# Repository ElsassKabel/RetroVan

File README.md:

# RetroVan
🚐 *Retro style [Minivan](https://trashman.wiki/keyboards/minivan) keyboard*

| Front side | Back side |
| ----- | ----- |
|  |  |

<!-- ## ✨ Pros:

- 🌈 Easy to customize with QMK and Vial
- 💅 Compact and beautiful
- 🦄 Open source -->

## 📖 Documentation

*🚧 WIP*

| Name | Supported layout |
| ----- | ----- |
| A | 1, 2 |
| B | 3, 4, 5 |
| C | 6, 7 |

<!-- ## 👀 Showcase -->

## 👤 Author

**LucasAlt**
* Website: https://www.lucasalt.fr
* Twitter: [@LucasCtrlAlt](https://twitter.com/LucasCtrlAlt)
* GitHub: [@LucasCtrl](https://github.com/LucasCtrl)

<!-- ## 🙏 Thanks
* [**@username**](https://github.com/username) - What I do
* [And many more!](https://github.com/ElsassKabel/RetroVan/graphs/contributors) -->

## 🤝 Contributing

<!-- Before contributing to this project, make sure you have read the [contribution guidelines](https://github.com/ElsassKabel/RetroVan/blob/main/CONTRIBUTING.md)! -->

1. Fork it (https://github.com/ElsassKabel/RetroVan/fork)
2. Create your feature branch (`git checkout -b feature/fooBar`)
3. Commit your changes (`git commit -am 'Add some fooBar'`)
4. Push to the branch (`git push origin feature/fooBar`)
5. Create a new Pull Request

## Show your support

- Give a ⭐️ if you like this project!

<!--  -->

## 📝 License

This project is open source and available under the [MIT License](https://github.com/ElsassKabel/RetroVan/blob/main/LICENSE.md)

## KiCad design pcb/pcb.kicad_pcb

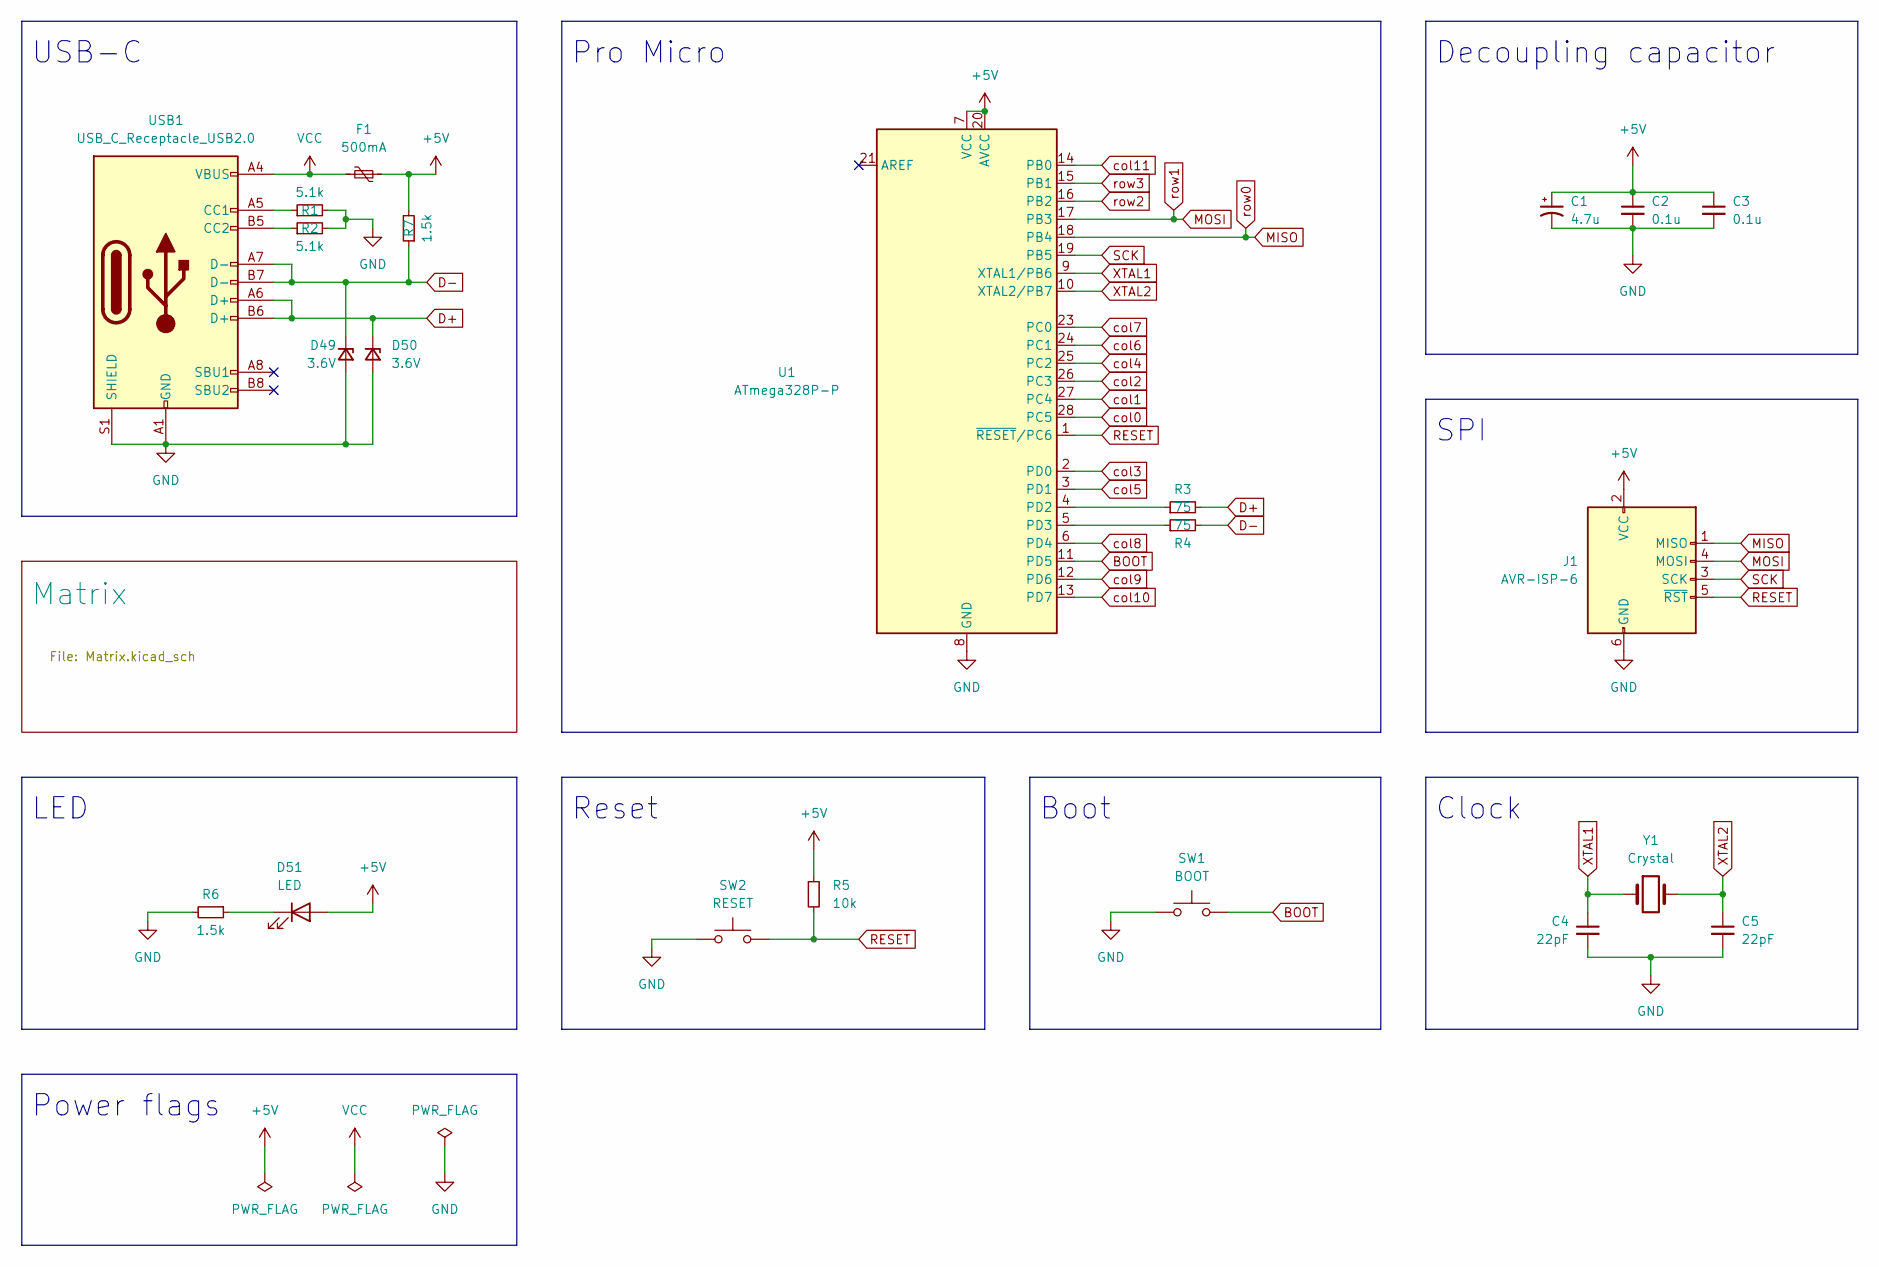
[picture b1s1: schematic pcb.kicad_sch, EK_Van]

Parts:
C1: 4.7u; CP_Radial_D4.0mm_P2.00mm
C2, C3: 0.1u; C_Disc_D4.3mm_W1.9mm_P5.00mm
C4, C5: 22pF; C_Disc_D3.0mm_W1.6mm_P2.50mm
D49, D50: 3.6V; D_DO-35_SOD27_P7.62mm_Horizontal
D51: LED; LED_D3.0mm
F1: 500mA; Fuse_Littelfuse_395Series
J1: AVR-ISP-6; PinHeader_2x03_P2.54mm_Vertical
R1, R2: 5.1k; R_Axial_DIN0204_L3.6mm_D1.6mm_P7.62mm_Horizontal
R3, R4: 75; R_Axial_DIN0204_L3.6mm_D1.6mm_P7.62mm_Horizontal
R5: 10k; R_Axial_DIN0204_L3.6mm_D1.6mm_P7.62mm_Horizontal
R6, R7: 1.5k; R_Axial_DIN0204_L3.6mm_D1.6mm_P7.62mm_Horizontal
SW1: BOOT; SW_PUSH_6mm
SW2: RESET; SW_PUSH_6mm
U1: ATmega328P-P; DIP-28_W7.62mm
USB1: USB_C_Receptacle_USB2.0; USB_C_GCT_USB4085
Y1: Crystal; Crystal_HC49-4H_Vertical

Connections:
+5V: C1.1, C2.1, C3.1, D51.2 (A), F1.1, J1.2 (VCC), R5.1, R7.2, U1.7 (VCC), U1.20 (AVCC)
BOOT: SW1.2, U1.11 (PD5)
D+: D50.1 (K), R3.2, USB1.A6 (D+), USB1.B6 (D+)
D-: D49.1 (K), R4.2, R7.1, USB1.A7 (D-), USB1.B7 (D-)
GND: C1.2, C2.2, C3.2, C4.2, C5.2, D49.2 (A), D50.2 (A), J1.6 (GND), R1.2, R2.2, R6.2, SW1.1, SW2.1, U1.8 (GND), U1.22 (GND), USB1.A1 (GND), USB1.A12 (GND), USB1.B1 (GND), USB1.B12 (GND), USB1.S1 (SHIELD)
MISO: J1.1 (MISO), U1.18 (PB4); also elsewhere on the board
MOSI: J1.4 (MOSI), U1.17 (PB3); also elsewhere on the board
unnamed: D51.1 (K), R6.1
unnamed: R1.1, USB1.A5 (CC1)
unnamed: R2.1, USB1.B5 (CC2)
unnamed: R3.1, U1.4 (PD2)
unnamed: R4.1, U1.5 (PD3)
RESET: J1.5 (~RST), R5.2, SW2.2, U1.1 (~RESET/PC6)
SCK: J1.3 (SCK), U1.19 (PB5)
VCC: F1.2, USB1.A4 (VBUS), USB1.A9 (VBUS), USB1.B4 (VBUS), USB1.B9 (VBUS)
XTAL1: C4.1, U1.9 (XTAL1/PB6), Y1.1
XTAL2: C5.1, U1.10 (XTAL2/PB7), Y1.2
col0: U1.28 (PC5); also elsewhere on the board
col1: U1.27 (PC4); also elsewhere on the board
col2: U1.26 (PC3); also elsewhere on the board
col3: U1.2 (PD0); also elsewhere on the board
col4: U1.25 (PC2); also elsewhere on the board
col5: U1.3 (PD1); also elsewhere on the board
col6: U1.24 (PC1); also elsewhere on the board
col7: U1.23 (PC0); also elsewhere on the board
col8: U1.6 (PD4); also elsewhere on the board
col9: U1.12 (PD6); also elsewhere on the board
col10: U1.13 (PD7); also elsewhere on the board
col11: U1.14 (PB0); also elsewhere on the board
row2: U1.16 (PB2); also elsewhere on the board
row3: U1.15 (PB1); also elsewhere on the board

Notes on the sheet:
LED
Power flags
SPI
Pro Micro
Decoupling capacitor
Clock
Boot
USB-C
Reset

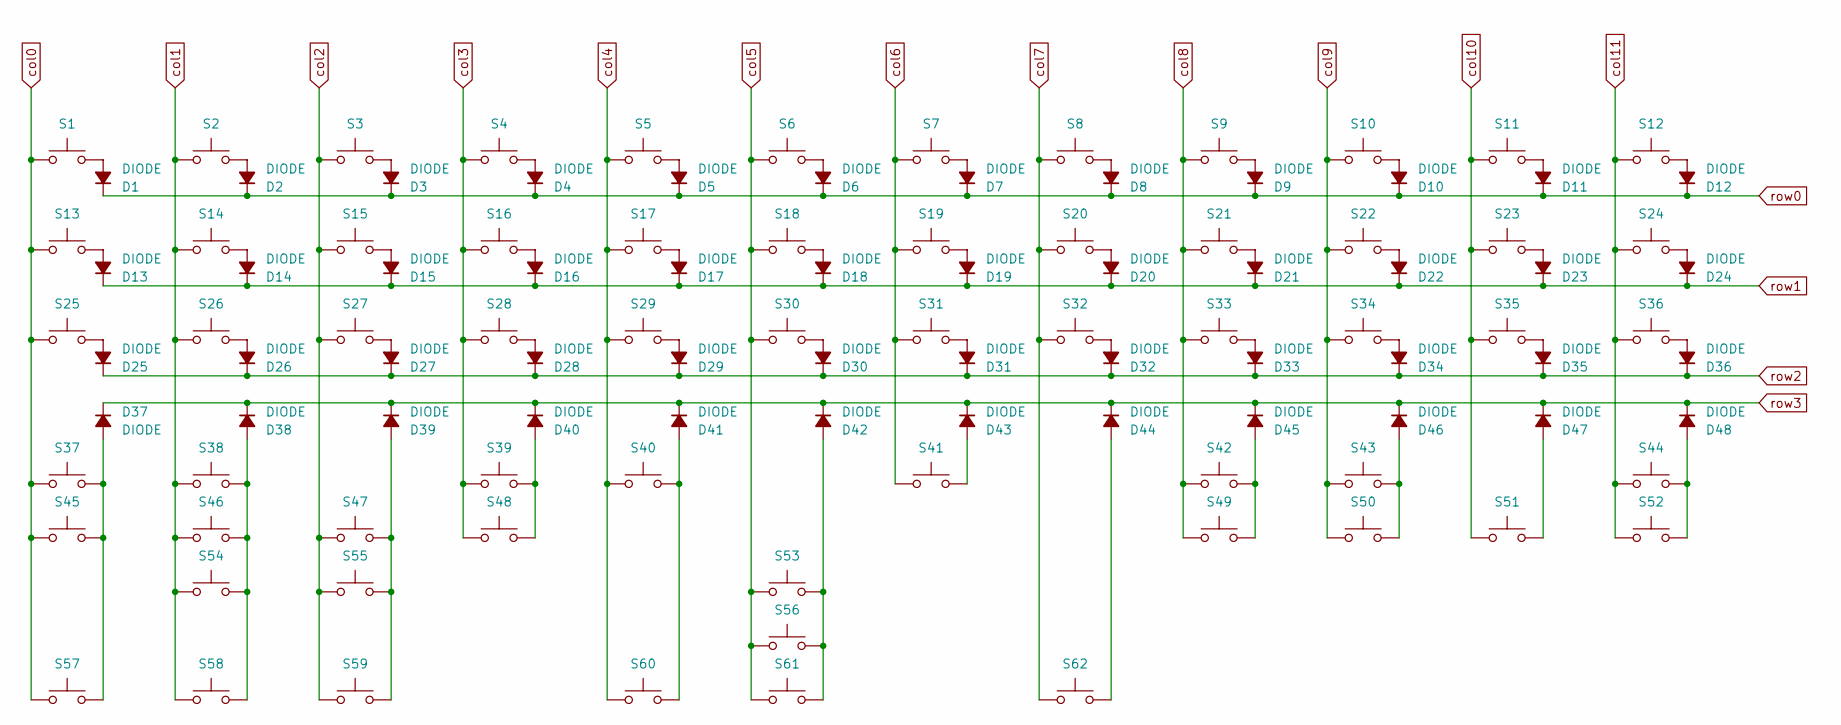
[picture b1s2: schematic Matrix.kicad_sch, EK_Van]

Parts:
D1, D2, D3, D4, D5, D6, D7, D8, D9, D10, D11, D12, D13, D14, D15, D16, D17, D18, D19, D20, D21, D22, D23, D24, D25, D26, D27, D28, D29, D30, D31, D32, D33, D34, D35, D36, D37, D38, D39, D40, D41, D42, D43, D44, D45, D46, D47, D48: DIODE; D_DO-35_SOD27_P7.62mm_Horizontal
S1, S2, S3, S4, S5, S6, S7, S8, S9, S10, S11, S14, S15, S16, S17, S18, S19, S20, S21, S22, S23, S26, S27, S28, S29, S30, S31, S32, S33, S34, S35, S36, S45, S46, S47, S48, S50, S51, S52, S54, S57, S59, S61: SWITCH_2PIN; SW_Cherry_MX_PCB_1.00u
S12, S25, S44: SWITCH_2PIN; SW_Cherry_MX_PCB_1.75u
S13, S37, S39, S42, S55, S58: SWITCH_2PIN; SW_Cherry_MX_PCB_1.25u
S24, S38, S43, S49: SWITCH_2PIN; SW_Cherry_MX_PCB_1.50u
S40, S60: SWITCH_2PIN; SW_Cherry_MX_PCB_2.25u
S41: SWITCH_2PIN; SW_Cherry_MX_PCB_2.00u
S53: SWITCH_2PIN; SW_Cherry_MX_PCB_6.25u
S56: SWITCH_2PIN; SW_Cherry_MX_PCB_7.00u
S62: SWITCH_2PIN; SW_Cherry_MX_PCB_2.75u

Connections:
MISO: D1.1 (K), D2.1 (K), D3.1 (K), D4.1 (K), D5.1 (K), D6.1 (K), D7.1 (K), D8.1 (K), D9.1 (K), D10.1 (K), D11.1 (K), D12.1 (K); also elsewhere on the board
MOSI: D13.1 (K), D14.1 (K), D15.1 (K), D16.1 (K), D17.1 (K), D18.1 (K), D19.1 (K), D20.1 (K), D21.1 (K), D22.1 (K), D23.1 (K), D24.1 (K); also elsewhere on the board
unnamed: D1.2 (A), S1.2
unnamed: D2.2 (A), S2.2
unnamed: D3.2 (A), S3.2
unnamed: D4.2 (A), S4.2
unnamed: D5.2 (A), S5.2
unnamed: D6.2 (A), S6.2
unnamed: D7.2 (A), S7.2
unnamed: D8.2 (A), S8.2
unnamed: D9.2 (A), S9.2
unnamed: D10.2 (A), S10.2
unnamed: D11.2 (A), S11.2
unnamed: D12.2 (A), S12.2
unnamed: D13.2 (A), S13.2
unnamed: D14.2 (A), S14.2
unnamed: D15.2 (A), S15.2
unnamed: D16.2 (A), S16.2
unnamed: D17.2 (A), S17.2
unnamed: D18.2 (A), S18.2
unnamed: D19.2 (A), S19.2
unnamed: D20.2 (A), S20.2
unnamed: D21.2 (A), S21.2
unnamed: D22.2 (A), S22.2
unnamed: D23.2 (A), S23.2
unnamed: D24.2 (A), S24.2
unnamed: D25.2 (A), S25.2
unnamed: D26.2 (A), S26.2
unnamed: D27.2 (A), S27.2
unnamed: D28.2 (A), S28.2
unnamed: D29.2 (A), S29.2
unnamed: D30.2 (A), S30.2
unnamed: D31.2 (A), S31.2
unnamed: D32.2 (A), S32.2
unnamed: D33.2 (A), S33.2
unnamed: D34.2 (A), S34.2
unnamed: D35.2 (A), S35.2
unnamed: D36.2 (A), S36.2
unnamed: D37.2 (A), S37.2, S45.2, S57.2
unnamed: D38.2 (A), S38.2, S46.2, S54.2, S58.2
unnamed: D39.2 (A), S47.2, S55.2, S59.2
unnamed: D40.2 (A), S39.2, S48.2
unnamed: D41.2 (A), S40.2, S60.2
unnamed: D42.2 (A), S53.2, S56.2, S61.2
unnamed: D43.2 (A), S41.2
unnamed: D44.2 (A), S62.2
unnamed: D45.2 (A), S42.2, S49.2
unnamed: D46.2 (A), S43.2, S50.2
unnamed: D47.2 (A), S51.2
unnamed: D48.2 (A), S44.2, S52.2
col0: S1.1, S13.1, S25.1, S37.1, S45.1, S57.1; also elsewhere on the board
col1: S2.1, S14.1, S26.1, S38.1, S46.1, S54.1, S58.1; also elsewhere on the board
col2: S3.1, S15.1, S27.1, S47.1, S55.1, S59.1; also elsewhere on the board
col3: S4.1, S16.1, S28.1, S39.1, S48.1; also elsewhere on the board
col4: S5.1, S17.1, S29.1, S40.1, S60.1; also elsewhere on the board
col5: S6.1, S18.1, S30.1, S53.1, S56.1, S61.1; also elsewhere on the board
col6: S7.1, S19.1, S31.1, S41.1; also elsewhere on the board
col7: S8.1, S20.1, S32.1, S62.1; also elsewhere on the board
col8: S9.1, S21.1, S33.1, S42.1, S49.1; also elsewhere on the board
col9: S10.1, S22.1, S34.1, S43.1, S50.1; also elsewhere on the board
col10: S11.1, S23.1, S35.1, S51.1; also elsewhere on the board
col11: S12.1, S24.1, S36.1, S44.1, S52.1; also elsewhere on the board
row2: D25.1 (K), D26.1 (K), D27.1 (K), D28.1 (K), D29.1 (K), D30.1 (K), D31.1 (K), D32.1 (K), D33.1 (K), D34.1 (K), D35.1 (K), D36.1 (K); also elsewhere on the board
row3: D37.1 (K), D38.1 (K), D39.1 (K), D40.1 (K), D41.1 (K), D42.1 (K), D43.1 (K), D44.1 (K), D45.1 (K), D46.1 (K), D47.1 (K), D48.1 (K); also elsewhere on the board

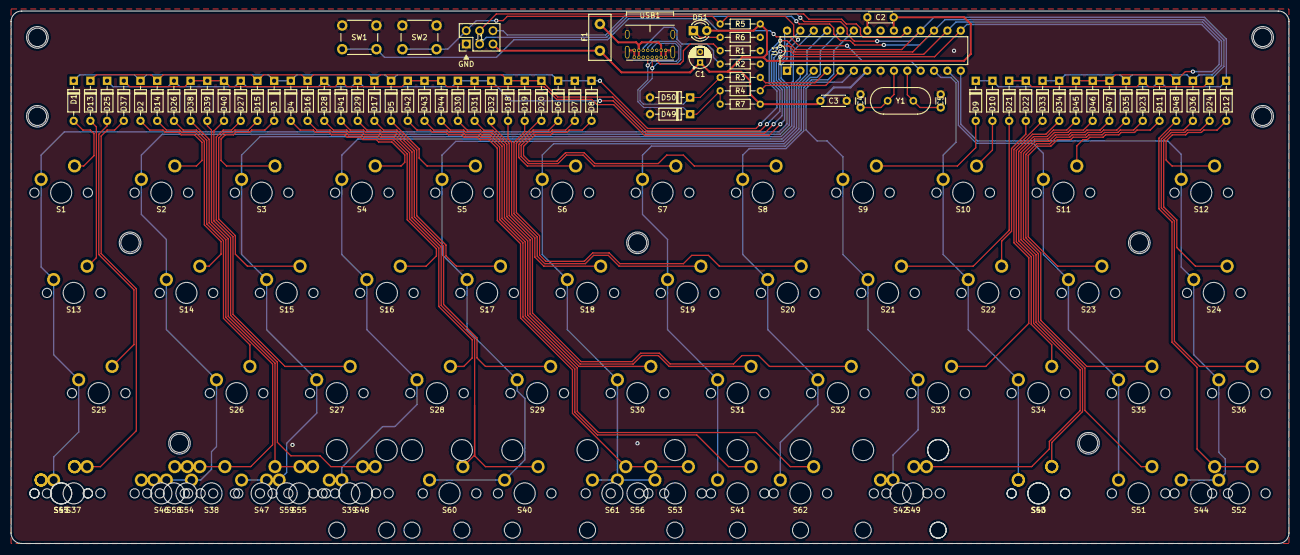
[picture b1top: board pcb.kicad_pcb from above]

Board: 2 copper layers, 242.9 x 101.2 mm, 132 parts (0 on the bottom side), 79 nets.

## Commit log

2022-11-18 🎉 Initial commit
2022-11-18 🚧 WIP - Create PCB schematic - Start to place components on the PCB
2022-11-18 ➕ Add submodules
2022-11-18 🚧 Fixing diodes footprints issue
2022-11-19 ➖ Remove submodule
2022-11-19 🚧 WIP - Place the components - Wire all the components
2022-11-27 ⬆️ Update local footprints
2022-11-27 🔖 PCB rev1 release
2022-12-02 🏗️ Prepare for production
2022-12-02 ✨ Add plate A
2022-12-02 ✨ Add back plate
2022-12-02 🚀 Add PCB gerber files
2022-12-02 🚀 Add plate A gerber files
2022-12-02 🚀 Add back plate gerber files
2022-12-03 ✨ Add BOM
2022-12-18 ✨ Add cover plate
2023-01-02 🛠️ Update LED resistor value
